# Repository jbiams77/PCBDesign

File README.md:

# PCBDesign
To manage my PCB Design files across multiple computers.

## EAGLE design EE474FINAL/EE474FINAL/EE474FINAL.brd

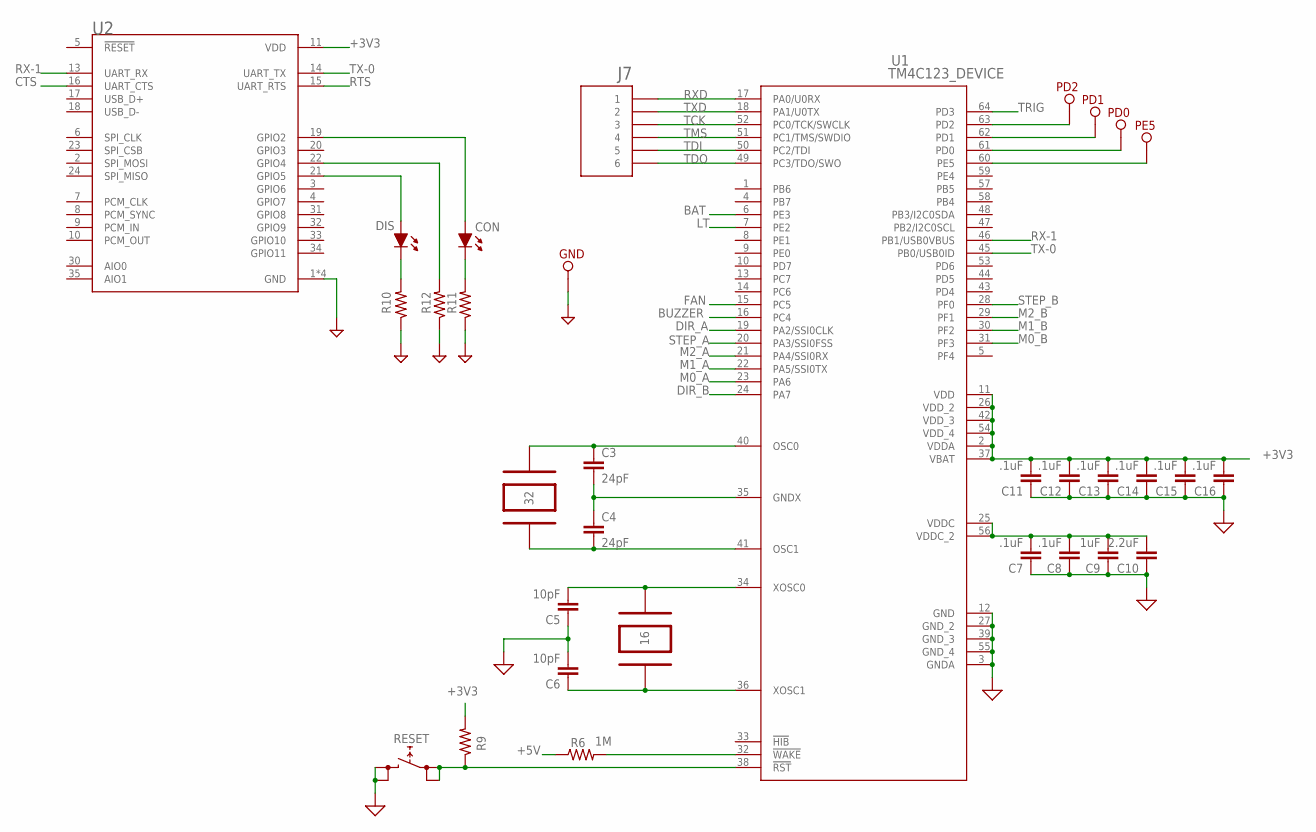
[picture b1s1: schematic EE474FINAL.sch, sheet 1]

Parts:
C3, C4: 24pF; CAPC1005X35N
C5, C6: 10pF; CAPC1005X35N
C7, C8, C11, C12, C13, C14, C15, C16: .1uF; CAPC1005X35N
C9: 1uF; CAPC1005X35N
C10: 2.2uF; CAPC1005X35N
CON: LED_511
DIS: LED_511
GND: TESTPOINT
J7: 6POS_JST
PD0, PD1, PD2: TESTPOINT
PE5: TESTPOINT
R6: 1M; CAPC1005X35N
R9, R10, R11, R12: RESISTOR; CAPC1005X35N
RESET: SWITCH_B3S; SW_BS3
U1: TM4C123_DEVICE; TM3C123_FOOTPRINT
U2: RN42-I/RM; XCVR_RN42-I/RM
Y1: 32kHz; GHI2_CRYSTAL_3.2X1.5
Y2: Y2; CRYSTAL_16MHZ

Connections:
!RST: R9.1, RESET.1, RESET.2, U1.38 (!RST)
!WAKE: R6.2, U1.32 (!WAKE)
+3V3: C11.2, C12.2, C13.2, C14.2, C15.2, C16.2, R9.2, U1.2 (VDDA), U1.11 (VDD), U1.26 (VDD_2), U1.37 (VBAT), U1.42 (VDD_3), U1.54 (VDD_4), U2.11 (VDD); also elsewhere on the board
+5V: R6.1; also elsewhere on the board
BAT: U1.6 (PE3); also elsewhere on the board
BUZZER: U1.16 (PC4); also elsewhere on the board
CTS: U2.16 (UART_CTS)
DIR_A: U1.19 (PA2/SSI0CLK); also elsewhere on the board
DIR_B: U1.24 (PA7); also elsewhere on the board
FAN: U1.15 (PC5); also elsewhere on the board
GND: C5.1, C6.2, C7.1, C8.1, C9.1, C10.1, C11.1, C12.1, C13.1, C14.1, C15.1, C16.1, GND.P$1, R10.1, R11.1, R12.1, RESET.3, RESET.4, U1.3 (GNDA), U1.12 (GND), U1.27 (GND_2), U1.39 (GND_3), U1.55 (GND_4), U2.1 (GND), U2.12 (GND), U2.28 (GND), U2.29 (GND); also elsewhere on the board
GNDX: C3.2, C4.1, U1.35 (GNDX)
LT: U1.7 (PE2); also elsewhere on the board
M0_A: U1.23 (PA6); also elsewhere on the board
M0_B: U1.31 (PF3); also elsewhere on the board
M1_A: U1.22 (PA5/SSI0TX); also elsewhere on the board
M1_B: U1.30 (PF2); also elsewhere on the board
M2_A: U1.21 (PA4/SSI0RX); also elsewhere on the board
M2_B: U1.29 (PF1); also elsewhere on the board
unnamed 36: U1.59 (PE4); also elsewhere on the board
unnamed: DIS.P$2 (2), U2.21 (GPIO5)
unnamed: DIS.P$1 (1), R10.2
unnamed: CON.P$1 (1), R11.2
unnamed: CON.P$2 (2), U2.19 (GPIO2)
unnamed: R12.2, U2.22 (GPIO4)
OSC0: C3.1, U1.40 (OSC0), Y1.P$2 (2)
OSC1: C4.2, U1.41 (OSC1), Y1.P$1 (1)
PD0: PD0.P$1, U1.61 (PD0)
PD1: PD1.P$1, U1.62 (PD1)
PD2: PD2.P$1, U1.63 (PD2)
PE5: PE5.P$1, U1.60 (PE5)
RTS: U2.15 (UART_RTS)
RX-1: U1.46 (PB1/USB0VBUS), U2.13 (UART_RX)
RXD: J7.6 (1), U1.17 (PA0/U0RX); also elsewhere on the board
STEP_A: U1.20 (PA3/SSI0FSS); also elsewhere on the board
STEP_B: U1.28 (PF0); also elsewhere on the board
TCK: J7.4 (3), U1.52 (PC0/TCK/SWCLK); also elsewhere on the board
TDI: J7.2 (5), U1.50 (PC2/TDI); also elsewhere on the board
TDO: J7.1 (6), U1.49 (PC3/TDO/SWO); also elsewhere on the board
TMS: J7.3 (4), U1.51 (PC1/TMS/SWDIO); also elsewhere on the board
TRIG: U1.64 (PD3); also elsewhere on the board
TX-0: U1.45 (PB0/USB0ID), U2.14 (UART_TX)
TXD: J7.5 (2), U1.18 (PA1/U0TX); also elsewhere on the board
VDDC: C7.2, C8.2, C9.2, C10.2, U1.25 (VDDC), U1.56 (VDDC_2)
XOSC0: C5.2, U1.34 (XOSC0), Y2.2
XOSC1: C6.1, U1.36 (XOSC1), Y2.1

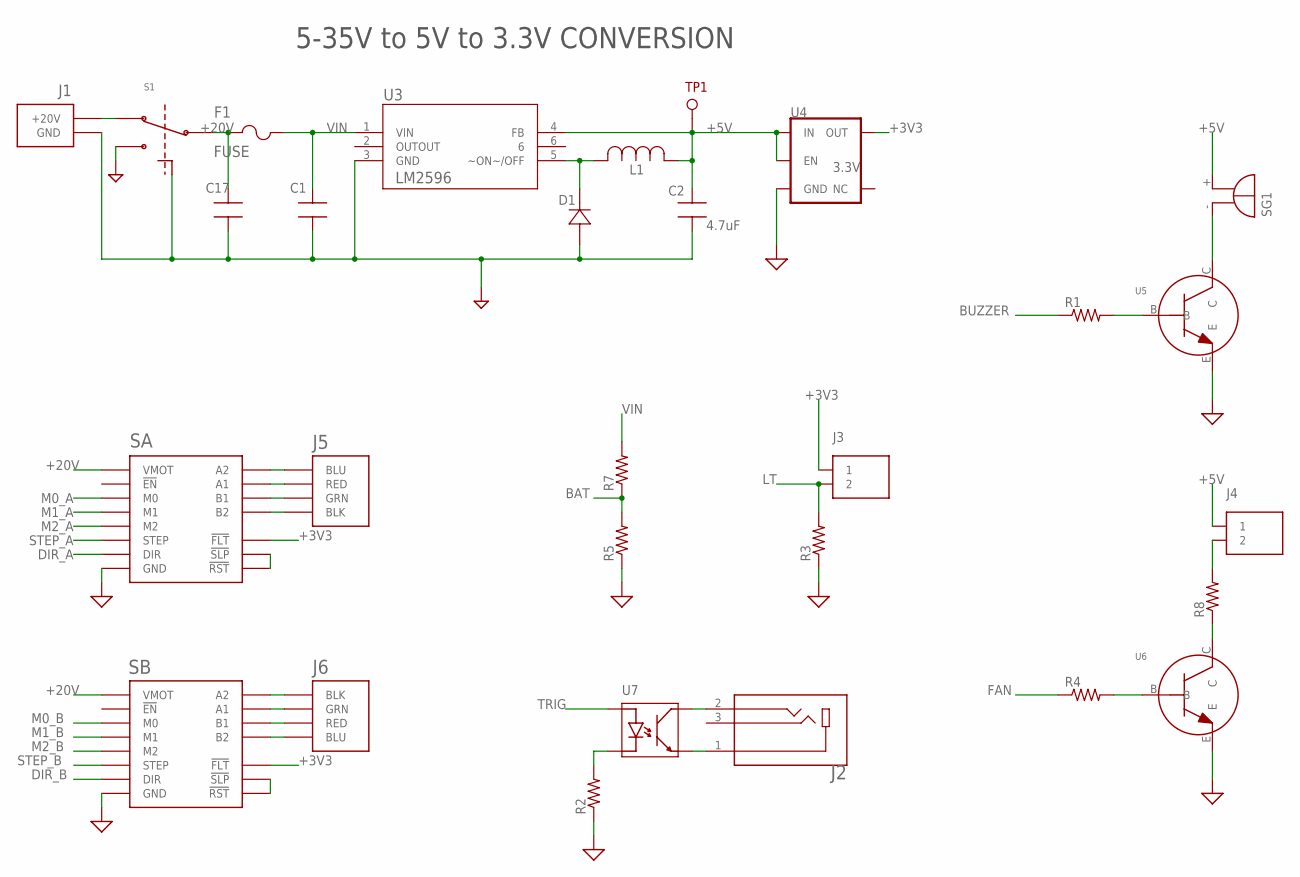
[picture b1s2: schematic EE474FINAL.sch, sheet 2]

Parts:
C1, C17: CAP_18; CAP_ULH_10X10
C2: 4.7uF; CAP_UCD_8X6P2
D1: DIODE_SHOTKY_SMA; SMA
F1: FUSE; FUS_VISHAY_MFU0805
J1: 2POS_JSTVERT_2.5; 2POS_JSTVERT
J2: AUDIOJACK
J3, J4: 2POS_JSTVERT_2.0; 2POS_JSTVERT_2.00
J5: 4POS_MOLEXVERT
J6: 4POS_MOLEX_2.54; MOLEX_0705530003
L1: INDUCTOR_SRR1210-680M; IND_BOURNS_SRR1210
R1, R2, R3, R4, R5, R7, R8: R-US_R0402; R0402
S1: SLIDESWITCH
SA: DRV8825
SB: DRV8825
SG1: F/QMBIII
TP1: TESTPOINT
U3: LM2596SX-5.0/NOPB; TS5B
U4: 3.3V; SOT23-5
U5, U6: NPN_BJT; SOT-23
U7: OPTOISOLATOR; SOP-4L_TC

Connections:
20IN: J1.P$1 (+20V), S1.1
+3V3: J3.1, SA.!FLT, SB.!FLT, U4.5 (OUT); also elsewhere on the board
+5V: C2.1, J4.1, L1.1, SG1.+ (-), TP1.P$1, U3.4 (FB), U4.1 (IN), U4.3 (EN); also elsewhere on the board
+20V: C17.1, F1.1, S1.2, SA.VMOT, SB.VMOT
BAT: R5.2, R7.1; also elsewhere on the board
BUZZER: R1.1; also elsewhere on the board
DIR_A: SA.DIR; also elsewhere on the board
DIR_B: SB.DIR; also elsewhere on the board
FAN: R4.1; also elsewhere on the board
FAN_OUT: J4.2, R8.2; also elsewhere on the board
GND: C1.2, C2.2, C17.2, D1.2, J1.P$2 (GND), R2.1, R3.1, R5.1, S1.3, S1.4 (GND), S1.5 (GND), SA.GND$1 (GND), SA.GND$2 (GND), SB.GND$1 (GND), SB.GND$2 (GND), U3.3 (GND), U4.2 (GND), U5.E, U6.E; also elsewhere on the board
LT: J3.2, R3.2; also elsewhere on the board
M0_A: SA.M0; also elsewhere on the board
M0_B: SB.M0; also elsewhere on the board
M1_A: SA.M1; also elsewhere on the board
M1_B: SB.M1; also elsewhere on the board
M2_A: SA.M2; also elsewhere on the board
M2_B: SB.M2; also elsewhere on the board
unnamed: R1.2, U5.B
unnamed 23: SG1.- (+), U5.C; also elsewhere on the board
unnamed: J2.2, U7.4
unnamed: J2.1, U7.3
unnamed: J6.4 (BLK), SB.A2
unnamed: R2.2, U7.2
unnamed: R4.2, U6.B
unnamed: J5.P$4 (BLU), SA.A2
unnamed: J5.P$3 (RED), SA.A1
unnamed: J5.P$2 (GRN), SA.B1
unnamed: J5.P$1 (BLK), SA.B2
unnamed: J6.3 (GRN), SB.A1
unnamed: J6.2 (RED), SB.B1
unnamed: J6.1 (BLU), SB.B2
unnamed: SB.!RST, SB.!SLP
unnamed: SA.!RST, SA.!SLP
unnamed: R8.1, U6.C
PWM: D1.1, L1.2, U3.5 (~ON~/OFF)
STEP_A: SA.STEP; also elsewhere on the board
STEP_B: SB.STEP; also elsewhere on the board
TRIG: U7.1; also elsewhere on the board
VIN: C1.1, F1.2, R7.2, U3.1 (VIN)

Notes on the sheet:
5-35V to 5V to 3.3V CONVERSION

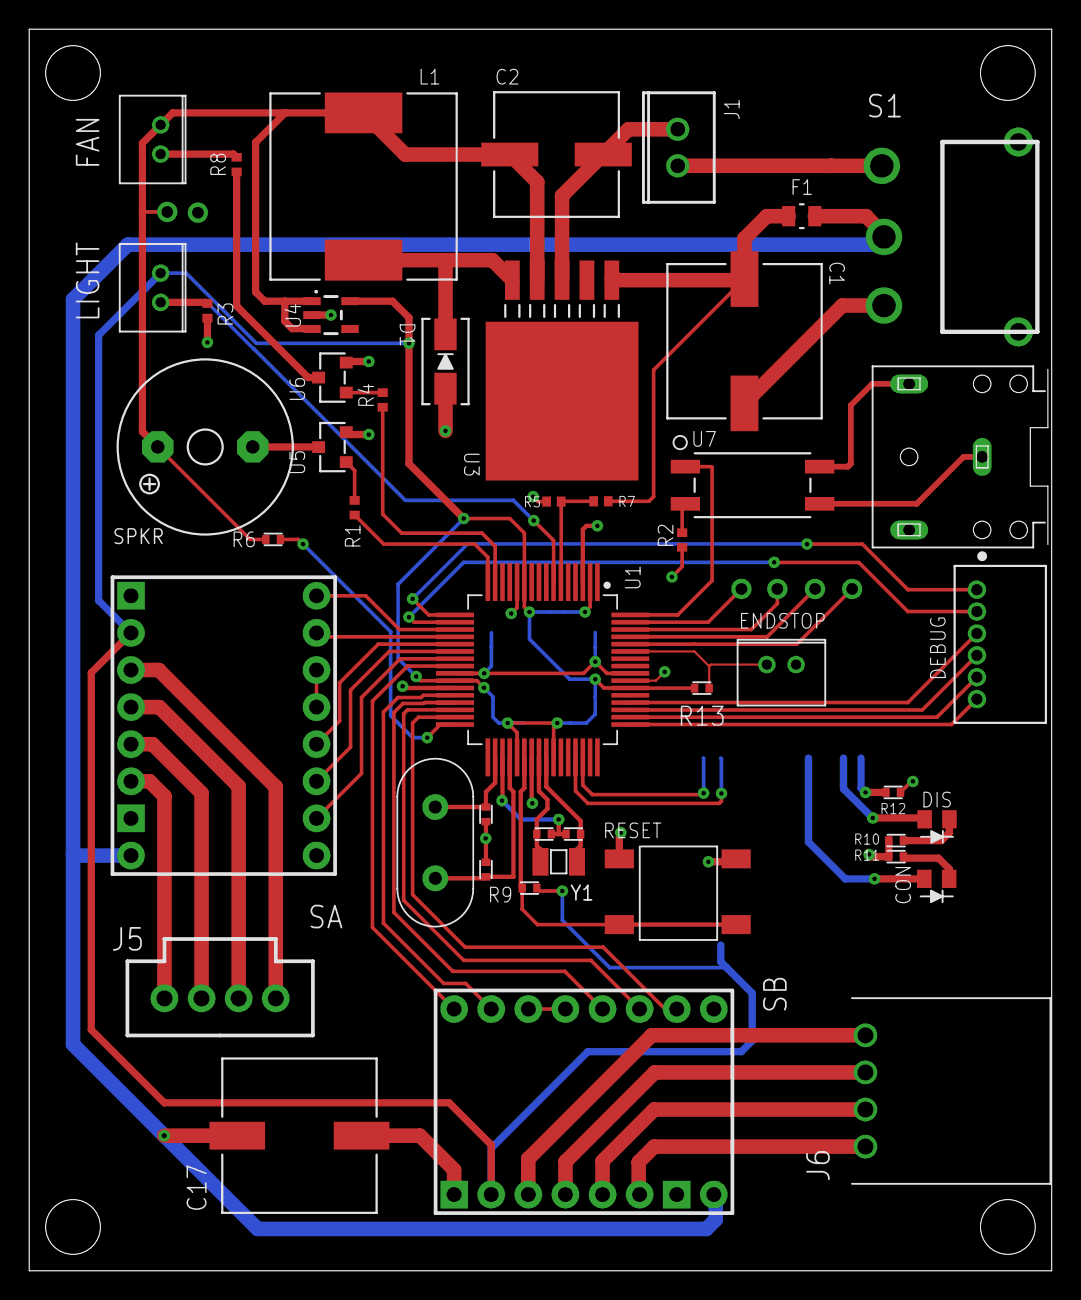
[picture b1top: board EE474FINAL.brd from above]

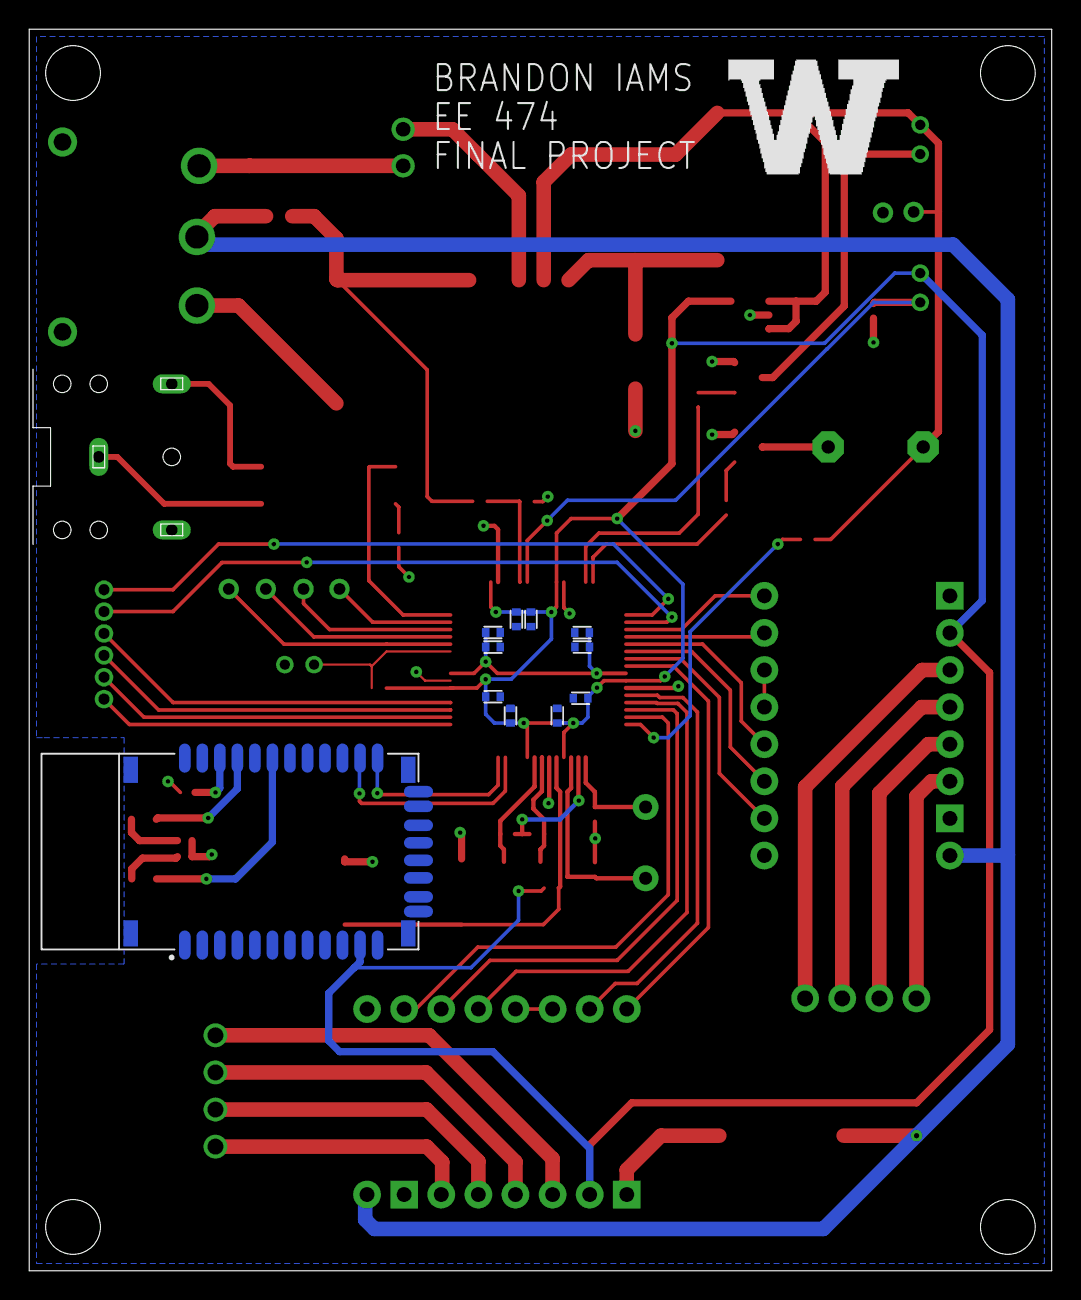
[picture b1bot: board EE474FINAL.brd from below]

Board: 2 copper layers, 70.0 x 85.0 mm, 64 parts (12 on the bottom side), 66 nets.

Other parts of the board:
DEBUG: 6POS_JST
ENDSTOP: 2POS_JSTVERT_2.00
FAN: 2POS_JSTVERT_2.00
LIGHT: 2POS_JSTVERT_2.00
R13: CAPC1005X35N
SPKR: F/QMBIII
U$1: LOGO_B

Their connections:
+3V3: LIGHT.1, R13.2; also elsewhere on the board
+5V: FAN.1, SPKR.+; also elsewhere on the board
FAN_OUT: FAN.2; also elsewhere on the board
GND: ENDSTOP.2; also elsewhere on the board
LT: LIGHT.2; also elsewhere on the board
unnamed 23: SPKR.-; also elsewhere on the board
unnamed 36: ENDSTOP.1, R13.1; also elsewhere on the board
RXD: DEBUG.6; also elsewhere on the board
TCK: DEBUG.4; also elsewhere on the board
TDI: DEBUG.2; also elsewhere on the board
TDO: DEBUG.1; also elsewhere on the board
TMS: DEBUG.3; also elsewhere on the board
TXD: DEBUG.5; also elsewhere on the board

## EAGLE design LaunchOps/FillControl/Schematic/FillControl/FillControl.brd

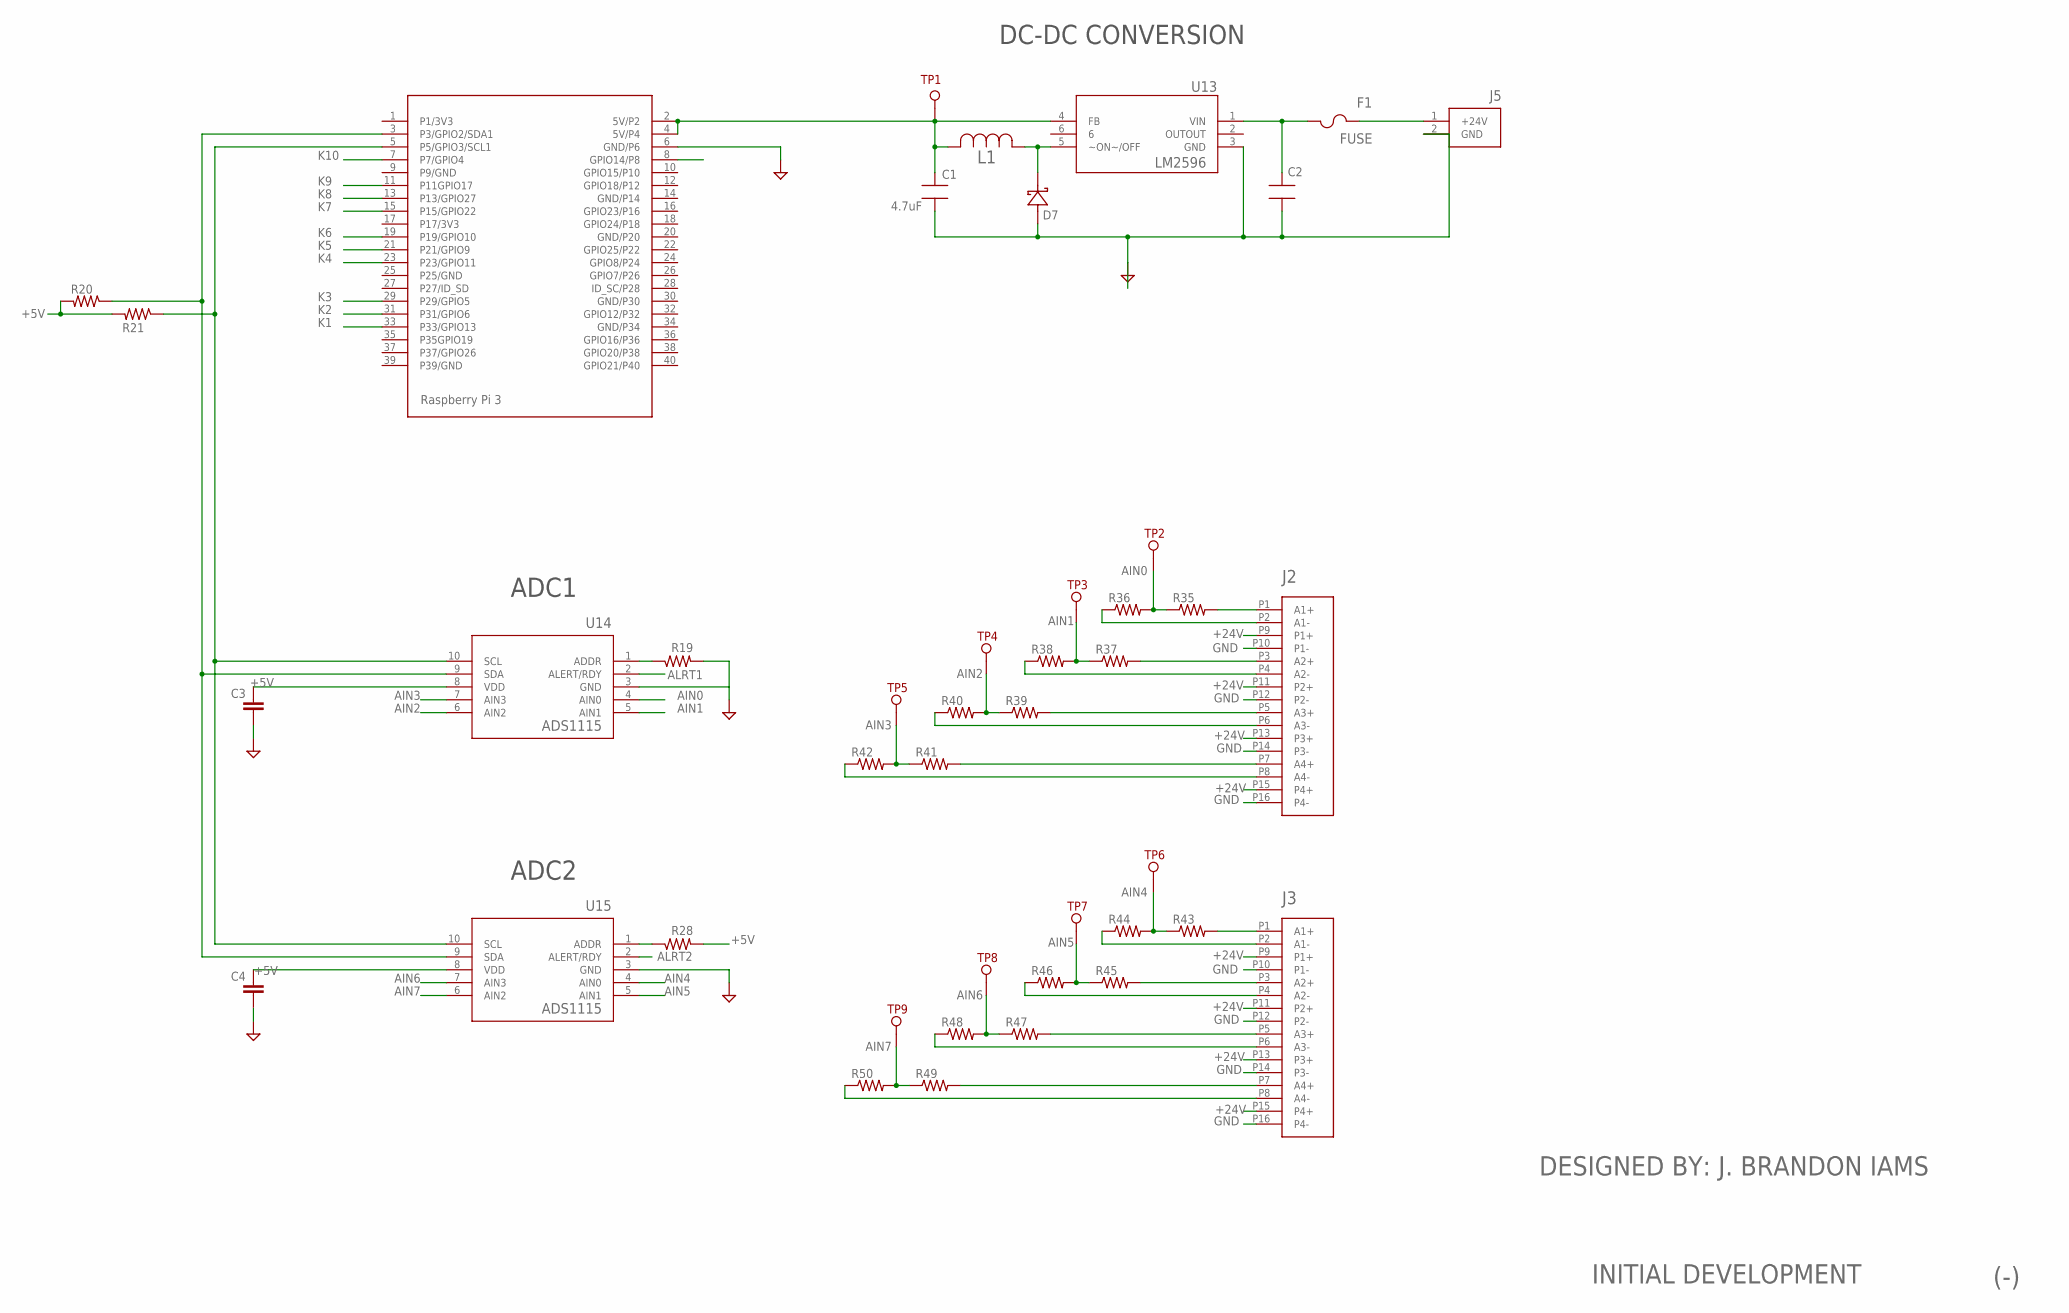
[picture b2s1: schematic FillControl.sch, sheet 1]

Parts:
C1: 4.7uF; CAP_UCD_8X6P2
C2: CAP_18; CAP_ULH_10X10
C3, C4: C-EUC0402; C0402
D7: SHOTKEY; SMC
F1: FUSE; FUS_VISHAY_MFU0805
J1: RASPBERRY-PI; 2X20_FEMALE_HEADER
J2, J3: 16POS_CONN; 16POS_MOLEX
J5: 2POS_SCREW; 2POS_BLOCK
L1: INDUCTOR_SRR1210-680M; IND_BOURNS_SRR1210
R19, R20, R21, R28, R35, R36, R37, R38, R39, R40, R41, R42, R43, R44, R45, R46, R47, R48, R49, R50: R-US_R0603; R0603
TP1, TP2, TP3, TP4, TP5, TP6, TP7, TP8, TP9: TESTPOINT
U13: LM2596SX-5.0/NOPB; TS5B
U14, U15: ADS1115IDGSR; DGS10

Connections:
+5V: C1.1, C3.1, C4.1, J1.2 (5V/P2), J1.4 (5V/P4), L1.1, R20.2, R21.2, R28.2, TP1.P$1, U13.4 (FB), U14.8 (VDD), U15.8 (VDD); also elsewhere on the board
+24V: F1.1, J2.P9 (P1+), J2.P11 (P2+), J2.P13 (P3+), J2.P15 (P4+), J3.P9 (P1+), J3.P11 (P2+), J3.P13 (P3+), J3.P15 (P4+), J5.1 (+24V); also elsewhere on the board
AIN0: R35.1, R36.2, TP2.P$1, U14.4 (AIN0)
AIN1: R37.1, R38.2, TP3.P$1, U14.5 (AIN1)
AIN2: R39.1, R40.2, TP4.P$1, U14.6 (AIN2)
AIN3: R41.1, R42.2, TP5.P$1, U14.7 (AIN3)
AIN4: R43.1, R44.2, TP6.P$1, U15.4 (AIN0)
AIN5: R45.1, R46.2, TP7.P$1, U15.5 (AIN1)
AIN6: R47.1, R48.2, TP8.P$1, U15.7 (AIN3)
AIN7: R49.1, R50.2, TP9.P$1, U15.6 (AIN2)
ALRT1: U14.2 (ALERT/RDY)
ALRT2: U15.2 (ALERT/RDY)
GND: C1.2, C2.2, C3.2, C4.2, D7.2, J1.6 (GND/P6), J2.P10 (P1-), J2.P12 (P2-), J2.P14 (P3-), J2.P16 (P4-), J3.P10 (P1-), J3.P12 (P2-), J3.P14 (P3-), J3.P16 (P4-), J5.2 (GND), U13.3 (GND), U15.3 (GND); also elsewhere on the board
K1: J1.33 (P33/GPIO13); also elsewhere on the board
K2: J1.31 (P31/GPIO6); also elsewhere on the board
K3: J1.29 (P29/GPIO5); also elsewhere on the board
K4: J1.23 (P23/GPIO11); also elsewhere on the board
K5: J1.21 (P21/GPIO9); also elsewhere on the board
K6: J1.19 (P19/GPIO10); also elsewhere on the board
K7: J1.15 (P15/GPIO22); also elsewhere on the board
K8: J1.13 (P13/GPIO27); also elsewhere on the board
K9: J1.11 (P11GPIO17); also elsewhere on the board
K10: J1.7 (P7/GPIO4); also elsewhere on the board
unnamed: J2.P2 (A1-), R36.1
unnamed: J2.P3 (A2+), R37.2
unnamed: J2.P4 (A2-), R38.1
unnamed: J2.P6 (A3-), R40.1
unnamed: J2.P5 (A3+), R39.2
unnamed: J2.P7 (A4+), R41.2
unnamed: J2.P8 (A4-), R42.1
unnamed: D7.1, L1.2, U13.5 (~ON~/OFF)
unnamed: J3.P1 (A1+), R43.2
unnamed: C2.1, F1.2, U13.1 (VIN)
unnamed: R19.1, U14.1 (ADDR)
unnamed: R28.1, U15.1 (ADDR)
unnamed: R19.2, U14.3 (GND)
unnamed: J2.P1 (A1+), R35.2
unnamed: J3.P2 (A1-), R44.1
unnamed: J3.P3 (A2+), R45.2
unnamed: J3.P4 (A2-), R46.1
unnamed: J3.P6 (A3-), R48.1
unnamed: J3.P5 (A3+), R47.2
unnamed: J3.P7 (A4+), R49.2
unnamed: J3.P8 (A4-), R50.1
SCL: J1.5 (P5/GPIO3/SCL1), R21.1, U14.10 (SCL), U15.10 (SCL)
SDA: J1.3 (P3/GPIO2/SDA1), R20.1, U14.9 (SDA), U15.9 (SDA)

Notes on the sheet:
DC-DC CONVERSION
ADC1
ADC2
INITIAL DEVELOPMENT
(-)
DESIGNED BY: J. BRANDON IAMS

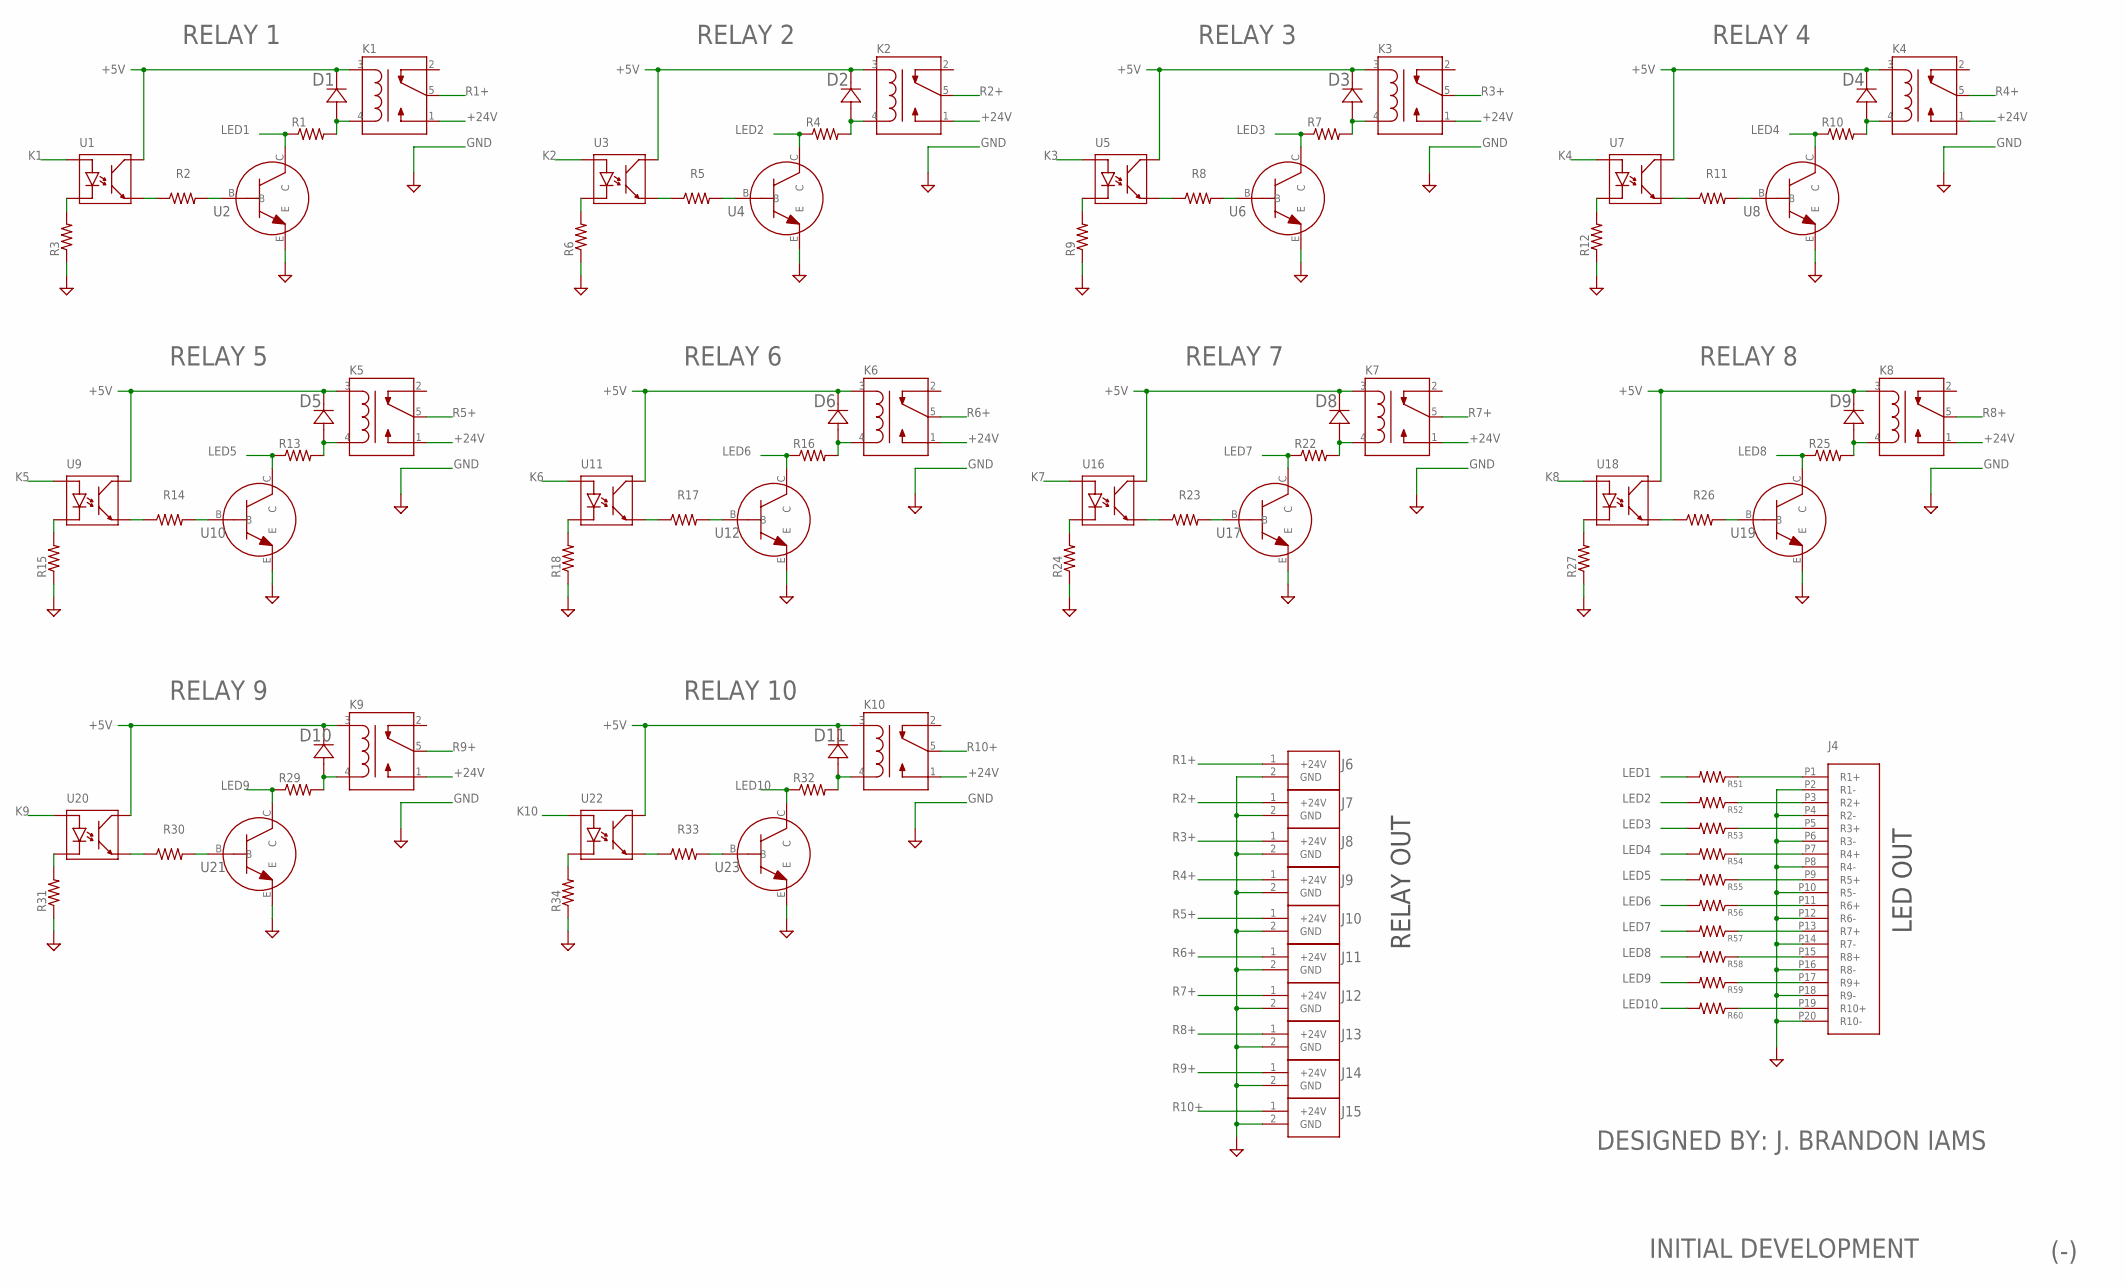
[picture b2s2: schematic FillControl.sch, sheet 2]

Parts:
D1, D2, D3, D4, D5, D6, D8, D9, D10, D11: DIODE; DIODE_SOD323
J4: 20POS_MOLEX
J6, J7, J8, J9, J10, J11, J12, J13, J14, J15: 2POS_SCREW; 2POS_BLOCK
K1, K2, K3, K4, K5, K6, K7, K8, K9, K10: RELAY; RELAY_1-1721150-0
R1, R2, R3, R4, R5, R6, R7, R8, R9, R10, R11, R12, R13, R14, R15, R16, R17, R18, R22, R23, R24, R25, R26, R27, R29, R30, R31, R32, R33, R34, R51, R52, R53, R54, R55, R56, R57, R58, R59, R60: R-US_R0603; R0603
U1, U3, U5, U7, U9, U11, U16, U18, U20, U22: OPTOISOLATOR; SOP-4L_TC
U2, U4, U6, U8, U10, U12, U17, U19, U21, U23: NPN_BJT; SOT-23

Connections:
+5V: D1.1, D2.1, D3.1, D4.1, D5.1, D6.1, D8.1, D9.1, D10.1, D11.1, K1.3, K2.3, K3.3, K4.3, K5.3, K6.3, K7.3, K8.3, K9.3, K10.3, U1.4, U3.4, U5.4, U7.4, U9.4, U11.4, U16.4, U18.4, U20.4, U22.4; also elsewhere on the board
+24V: K1.1, K2.1, K3.1, K4.1, K5.1, K6.1, K7.1, K8.1, K9.1, K10.1; also elsewhere on the board
GND: J4.P2 (R1-), J4.P4 (R2-), J4.P6 (R3-), J4.P8 (R4-), J4.P10 (R5-), J4.P12 (R6-), J4.P14 (R7-), J4.P16 (R8-), J4.P18 (R9-), J4.P20 (R10-), J6.2 (GND), J7.2 (GND), J8.2 (GND), J9.2 (GND), J10.2 (GND), J11.2 (GND), J12.2 (GND), J13.2 (GND), J14.2 (GND), J15.2 (GND), R3.1, R6.1, R9.1, R12.1, R15.1, R18.1, R24.1, R27.1, R31.1, R34.1, U2.E, U4.E, U6.E, U8.E, U10.E, U12.E, U17.E, U19.E, U21.E, U23.E; also elsewhere on the board
K1: U1.1; also elsewhere on the board
K2: U3.1; also elsewhere on the board
K3: U5.1; also elsewhere on the board
K4: U7.1; also elsewhere on the board
K5: U9.1; also elsewhere on the board
K6: U11.1; also elsewhere on the board
K7: U16.1; also elsewhere on the board
K8: U18.1; also elsewhere on the board
K9: U20.1; also elsewhere on the board
K10: U22.1; also elsewhere on the board
LED1: R1.1, R51.2, U2.C
LED2: R4.1, R52.2, U4.C
LED3: R7.1, R53.2, U6.C
LED4: R10.1, R54.2, U8.C
LED5: R13.1, R55.2, U10.C
LED6: R16.1, R56.2, U12.C
LED7: R22.1, R57.2, U17.C
LED8: R25.1, R58.2, U19.C
LED9: R29.1, R59.2, U21.C
LED10: R32.1, R60.2, U23.C
unnamed: R2.1, U1.3
unnamed: D1.2, K1.4, R1.2
unnamed: R2.2, U2.B
unnamed: J4.P1 (R1+), R51.1
unnamed: R3.2, U1.2
unnamed: J4.P5 (R3+), R53.1
unnamed: D2.2, K2.4, R4.2
unnamed: R5.1, U3.3
unnamed: R5.2, U4.B
unnamed: J4.P3 (R2+), R52.1
unnamed: R6.2, U3.2
unnamed: J4.P7 (R4+), R54.1
unnamed: D3.2, K3.4, R7.2
unnamed: R8.1, U5.3
unnamed: R8.2, U6.B
unnamed: J4.P9 (R5+), R55.1
unnamed: R9.2, U5.2
unnamed: J4.P11 (R6+), R56.1
unnamed: D4.2, K4.4, R10.2
unnamed: R11.1, U7.3
unnamed: R11.2, U8.B
unnamed: J4.P13 (R7+), R57.1
unnamed: R12.2, U7.2
unnamed: J4.P15 (R8+), R58.1
unnamed: D5.2, K5.4, R13.2
unnamed: R14.1, U9.3
unnamed: R14.2, U10.B
unnamed: J4.P17 (R9+), R59.1
unnamed: R15.2, U9.2
unnamed: J4.P19 (R10+), R60.1
unnamed: D6.2, K6.4, R16.2
unnamed: R17.1, U11.3
unnamed: R17.2, U12.B
unnamed: R18.2, U11.2
unnamed: D8.2, K7.4, R22.2
unnamed: R23.1, U16.3
unnamed: R23.2, U17.B
unnamed: R24.2, U16.2
unnamed: D9.2, K8.4, R25.2
unnamed: R26.1, U18.3
unnamed: R26.2, U19.B
unnamed: R27.2, U18.2
unnamed: D10.2, K9.4, R29.2
unnamed: R30.1, U20.3
unnamed: R30.2, U21.B
unnamed: R31.2, U20.2
unnamed: D11.2, K10.4, R32.2
unnamed: R33.1, U22.3
unnamed: R33.2, U23.B
unnamed: R34.2, U22.2
R1+: J6.1 (+24V), K1.5
R2+: J7.1 (+24V), K2.5
R3+: J8.1 (+24V), K3.5
R4+: J9.1 (+24V), K4.5
R5+: J10.1 (+24V), K5.5
R6+: J11.1 (+24V), K6.5
R7+: J12.1 (+24V), K7.5
R8+: J13.1 (+24V), K8.5
R9+: J14.1 (+24V), K9.5
R10+: J15.1 (+24V), K10.5

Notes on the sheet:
RELAY 1
RELAY 2
RELAY 3
RELAY 4
RELAY 5
RELAY 6
RELAY 7
RELAY 8
RELAY 9
RELAY 10
RELAY OUT
LED OUT
INITIAL DEVELOPMENT
(-)
DESIGNED BY: J. BRANDON IAMS

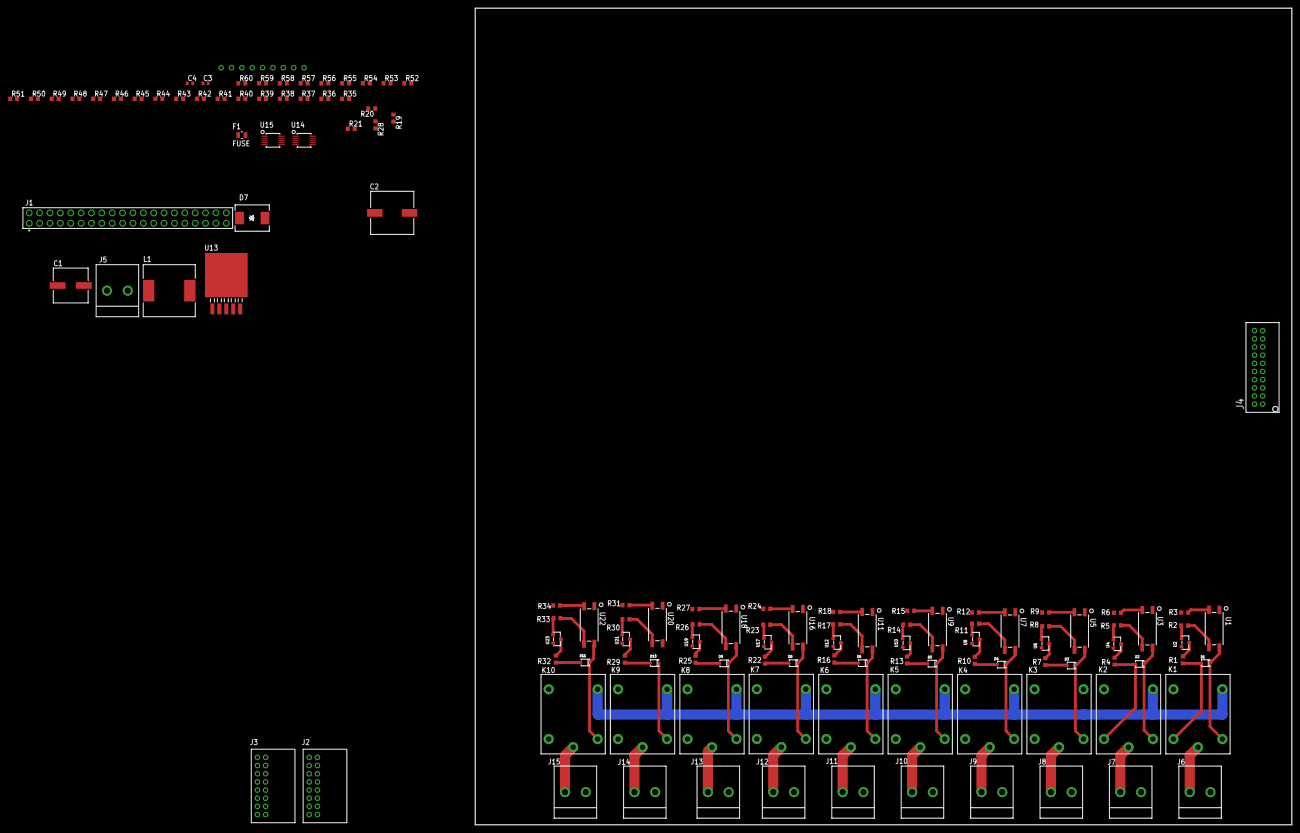
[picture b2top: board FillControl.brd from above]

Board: 2 copper layers, 200.0 x 200.0 mm, 134 parts (0 on the bottom side), 114 nets.

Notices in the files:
parts and their libraries:
SparkFun-IC-Power: Licensing: Creative Commons ShareAlike 4.0 International - https://creativecommons.org/licenses/by-sa/4.0
